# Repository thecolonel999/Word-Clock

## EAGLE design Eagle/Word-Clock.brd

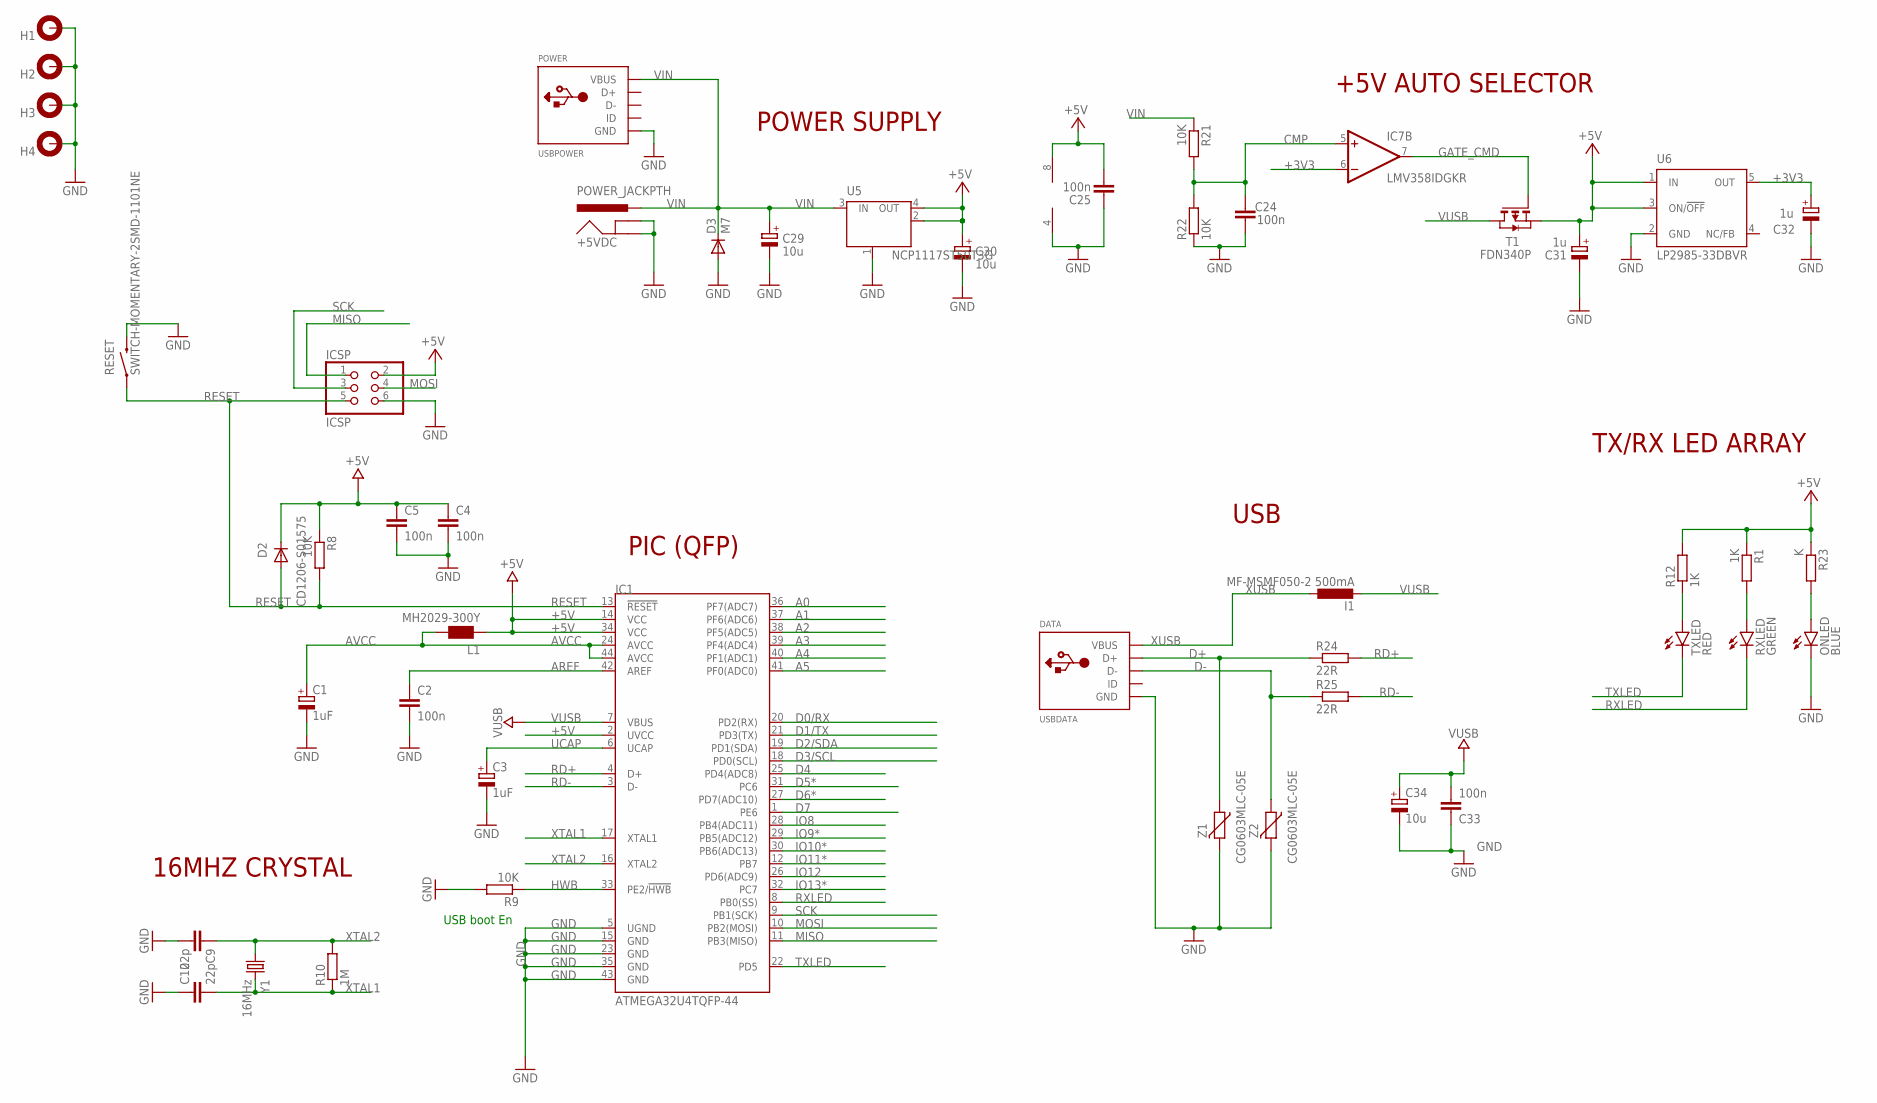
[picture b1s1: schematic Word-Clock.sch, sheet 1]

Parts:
+5VDC: POWER_JACKPTH; POWER_JACK_PTH
C1, C3: 1uF; B/3528-21W
C2, C4, C5, C24, C25, C33: 100n; C1206
C9, C10: 22p; C1206
C29, C30, C34: 10u; B/3528-21W
C31, C32: 1u; B/3528-21W
D2: CD1206-S01575; MINIMELF
D3: M7; SMB
DATA: USBDATA; USB-MINIB-THM-MOLEX
H1, H2, H3, H4: MOUNT-PAD-ROUND2.8; 2,8-PAD
I1: MF-MSMF050-2 500mA; L1812
IC1: ATMEGA32U4TQFP-44; TQFP44
IC7: LMV358IDGKR; SO08
ICSP: ICSP; 2X03/90
L1: MH2029-300Y; 0805
ONLED: BLUE; LED-1206; FARNELL 2322084
POWER: USBPOWER; USB-MINIB-THM-MOLEX
R1, R12: 1K; R1206
R8, R9, R21, R22: 10K; R1206
R10: 1M; R1206
R23: K; R1206
R24, R25: 22R; R1206
RESET: SWITCH-MOMENTARY-2SMD-1101NE; TACTILE-SWITCH-1101NE
RXLED: GREEN; LED-1206; FARNELL 2322085
T1: FDN340P; SOT-23
TXLED: RED; LED-1206
U5: NCP1117ST50T3G; SOT223; FARNELL 1147874
U6: LP2985-33DBVR; SOT23-DBV
Y1: 16MHz; HC49UP
Z1, Z2: CG0603MLC-05E; CT/CN0603

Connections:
+3V3: C32.+, IC7.6 (-IN), U6.5 (OUT)
+5V: C4.1, C5.1, C25.2, C30.+, C31.+, D2.C, IC1.2 (UVCC), IC1.14 (VCC), IC1.34 (VCC), IC7.8 (V+), ICSP.2, L1.1, R1.1, R8.1, R12.2, R23.1, T1.2 (S), U5.2 (OUT), U5.4 (OUT), U6.1 (IN), U6.3 (ON/!OFF); also elsewhere on the board
A0: IC1.36 (PF7(ADC7)); also elsewhere on the board
A1: IC1.37 (PF6(ADC6)); also elsewhere on the board
A2: IC1.38 (PF5(ADC5)); also elsewhere on the board
A3: IC1.39 (PF4(ADC4)); also elsewhere on the board
A4: IC1.40 (PF1(ADC1)); also elsewhere on the board
A5: IC1.41 (PF0(ADC0)); also elsewhere on the board
AREF: C2.1, IC1.42 (AREF)
AVCC: C1.+, IC1.24 (AVCC), IC1.44 (AVCC), L1.2
CMP: C24.2, IC7.5 (+IN), R21.2, R22.2
D0/RX: IC1.20 (PD2(RX)); also elsewhere on the board
D1/TX: IC1.21 (PD3(TX)); also elsewhere on the board
D2/SDA: IC1.19 (PD1(SDA)); also elsewhere on the board
D3/SCL: IC1.18 (PD0(SCL)); also elsewhere on the board
D4: IC1.25 (PD4(ADC8)); also elsewhere on the board
D5*: IC1.31 (PC6); also elsewhere on the board
D6*: IC1.27 (PD7(ADC10)); also elsewhere on the board
D7: IC1.1 (PE6); also elsewhere on the board
D+: DATA.D+, R24.1, Z1.1
D-: DATA.D-, R25.1, Z2.1
GATE_CMD: IC7.7 (OUT), T1.3 (G)
GND: +5VDC.GND, +5VDC.GNDBREAK, C1.-, C2.2, C3.-, C4.2, C5.2, C9.2, C10.1, C24.1, C25.1, C29.-, C30.-, C31.-, C32.-, C33.1, C34.-, D3.A, DATA.GND, H1.B2,8, H2.B2,8, H3.B2,8, H4.B2,8, IC1.5 (UGND), IC1.15 (GND), IC1.23 (GND), IC1.35 (GND), IC1.43 (GND), IC7.4 (V-), ICSP.6, ONLED.C, POWER.GND, R9.2, R22.1, RESET.2, U5.1 (GND/ADJ), U6.2 (GND), Z1.2, Z2.2; also elsewhere on the board
HWB: IC1.33 (PE2/!HWB), R9.1
IO8: IC1.28 (PB4(ADC11)); also elsewhere on the board
IO9*: IC1.29 (PB5(ADC12)); also elsewhere on the board
IO10*: IC1.30 (PB6(ADC13)); also elsewhere on the board
IO11*: IC1.12 (PB7); also elsewhere on the board
IO12: IC1.26 (PD6(ADC9)); also elsewhere on the board
IO13*: IC1.32 (PC7); also elsewhere on the board
MISO: IC1.11 (PB3(MISO)), ICSP.1
MOSI: IC1.10 (PB2(MOSI)), ICSP.4
unnamed: R12.1, TXLED.A
unnamed: R1.2, RXLED.A
unnamed: ONLED.A, R23.2
RD+: IC1.4 (D+), R24.2
RD-: IC1.3 (D-), R25.2
RESET: D2.A, IC1.13 (!RESET), ICSP.5, R8.2, RESET.1
RXLED: IC1.8 (PB0(SS)), RXLED.C
SCK: IC1.9 (PB1(SCK)), ICSP.3
TXLED: IC1.22 (PD5), TXLED.C
UCAP: C3.+, IC1.6 (UCAP)
VIN: +5VDC.PWR, C29.+, D3.C, POWER.VBUS, R21.1, U5.3 (IN); also elsewhere on the board
VUSB: C33.2, C34.+, I1.2, IC1.7 (VBUS), T1.1 (D)
XTAL1: C10.2, IC1.17 (XTAL1), R10.1, Y1.2
XTAL2: C9.1, IC1.16 (XTAL2), R10.2, Y1.1
XUSB: DATA.VBUS, I1.1

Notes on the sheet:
USB boot En
USB
+5V AUTO SELECTOR
PIC (QFP)
TX/RX LED ARRAY
16MHZ CRYSTAL
POWER SUPPLY

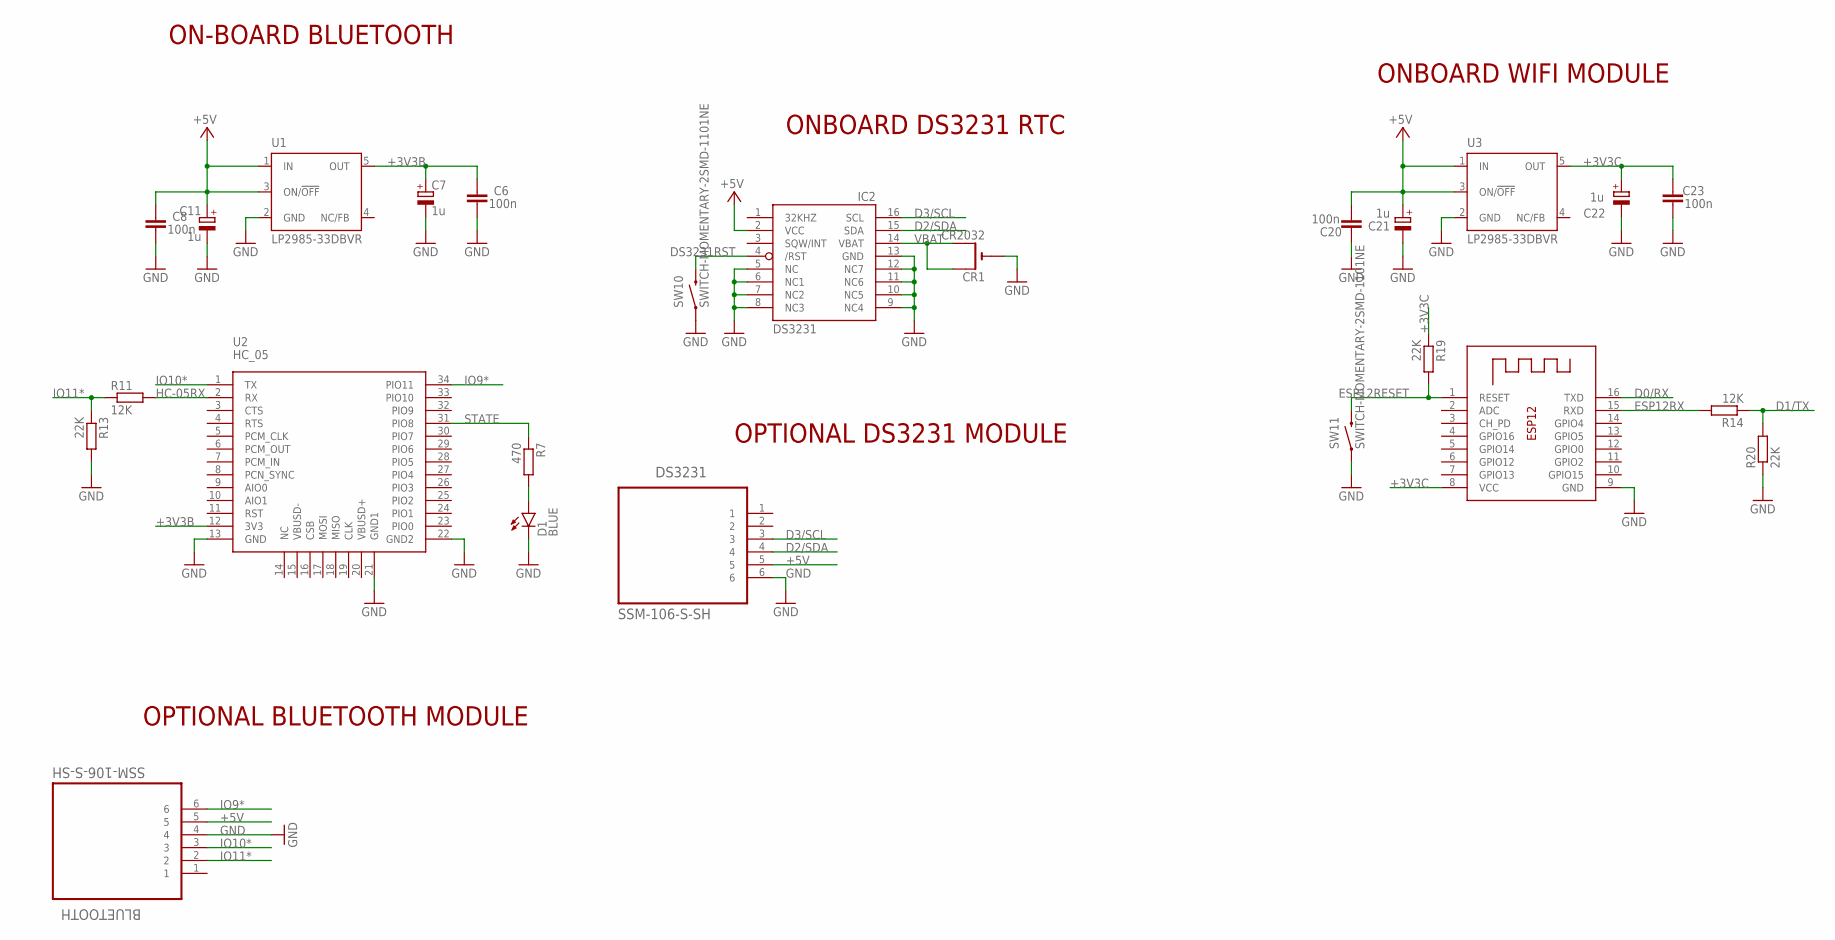
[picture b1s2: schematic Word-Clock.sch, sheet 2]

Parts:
BLUETOOTH: SSM-106-S-SH; SAMTEC_SSM-106-S-SH
C6, C8, C20, C23: 100n; C1206
C7, C11, C21, C22: 1u; B/3528-21W
CR1: CR2032; CR2032-SMD
D1: BLUE; LED-1206
DS3231: SSM-106-S-SH; SAMTEC_SSM-106-S-SH
ESP12: ESP12; ESP-12
IC2: DS3231/SO; SO16W
R7: 470; R1206
R11, R14: 12K; R1206
R13, R19, R20: 22K; R1206
SW10, SW11: SWITCH-MOMENTARY-2SMD-1101NE; TACTILE-SWITCH-1101NE
U1, U3: LP2985-33DBVR; SOT23-DBV
U2: HC_05; BLUETOOTH_SMD

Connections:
+3V3B: C6.2, C7.+, U1.5 (OUT), U2.12 (3V3)
+3V3C: C22.+, C23.2, ESP12.8 (VCC), R19.1, U3.5 (OUT)
+5V: BLUETOOTH.5, C8.2, C11.+, C20.1, C21.+, DS3231.5, IC2.2 (VCC), U1.1 (IN), U1.3 (ON/!OFF), U3.1 (IN), U3.3 (ON/!OFF); also elsewhere on the board
BLUETOOTHLED: D1.A, R7.2
D0/RX: ESP12.16 (TXD); also elsewhere on the board
D1/TX: R14.1, R20.2; also elsewhere on the board
D2/SDA: DS3231.4, IC2.15 (SDA); also elsewhere on the board
D3/SCL: DS3231.3, IC2.16 (SCL); also elsewhere on the board
DS3231RST: IC2.4 (/RST), SW10.2
ESP12RESET: ESP12.1 (RESET), R19.2, SW11.2
ESP12RX: ESP12.15 (RXD), R14.2
GND: BLUETOOTH.4, C6.1, C7.-, C8.1, C11.-, C20.2, C21.-, C22.-, C23.1, CR1.-, D1.C, DS3231.6, ESP12.9 (GND), IC2.5 (NC), IC2.6 (NC1), IC2.7 (NC2), IC2.8 (NC3), IC2.9 (NC4), IC2.10 (NC5), IC2.11 (NC6), IC2.12 (NC7), IC2.13 (GND), R13.2, R20.1, SW10.1, SW11.1, U1.2 (GND), U2.13 (GND), U2.21 (GND1), U2.22 (GND2), U3.2 (GND); also elsewhere on the board
HC-05RX: R11.2, U2.2 (RX)
IO9*: BLUETOOTH.6, U2.34 (PIO11); also elsewhere on the board
IO10*: BLUETOOTH.3, U2.1 (TX); also elsewhere on the board
IO11*: BLUETOOTH.2, R11.1, R13.1; also elsewhere on the board
STATE: R7.1, U2.31 (PIO8)
VBAT: CR1.+$1 (+), CR1.+$2 (+1), IC2.14 (VBAT)

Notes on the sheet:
ONBOARD DS3231 RTC
OPTIONAL BLUETOOTH MODULE
ON-BOARD BLUETOOTH
OPTIONAL DS3231 MODULE
ONBOARD WIFI MODULE

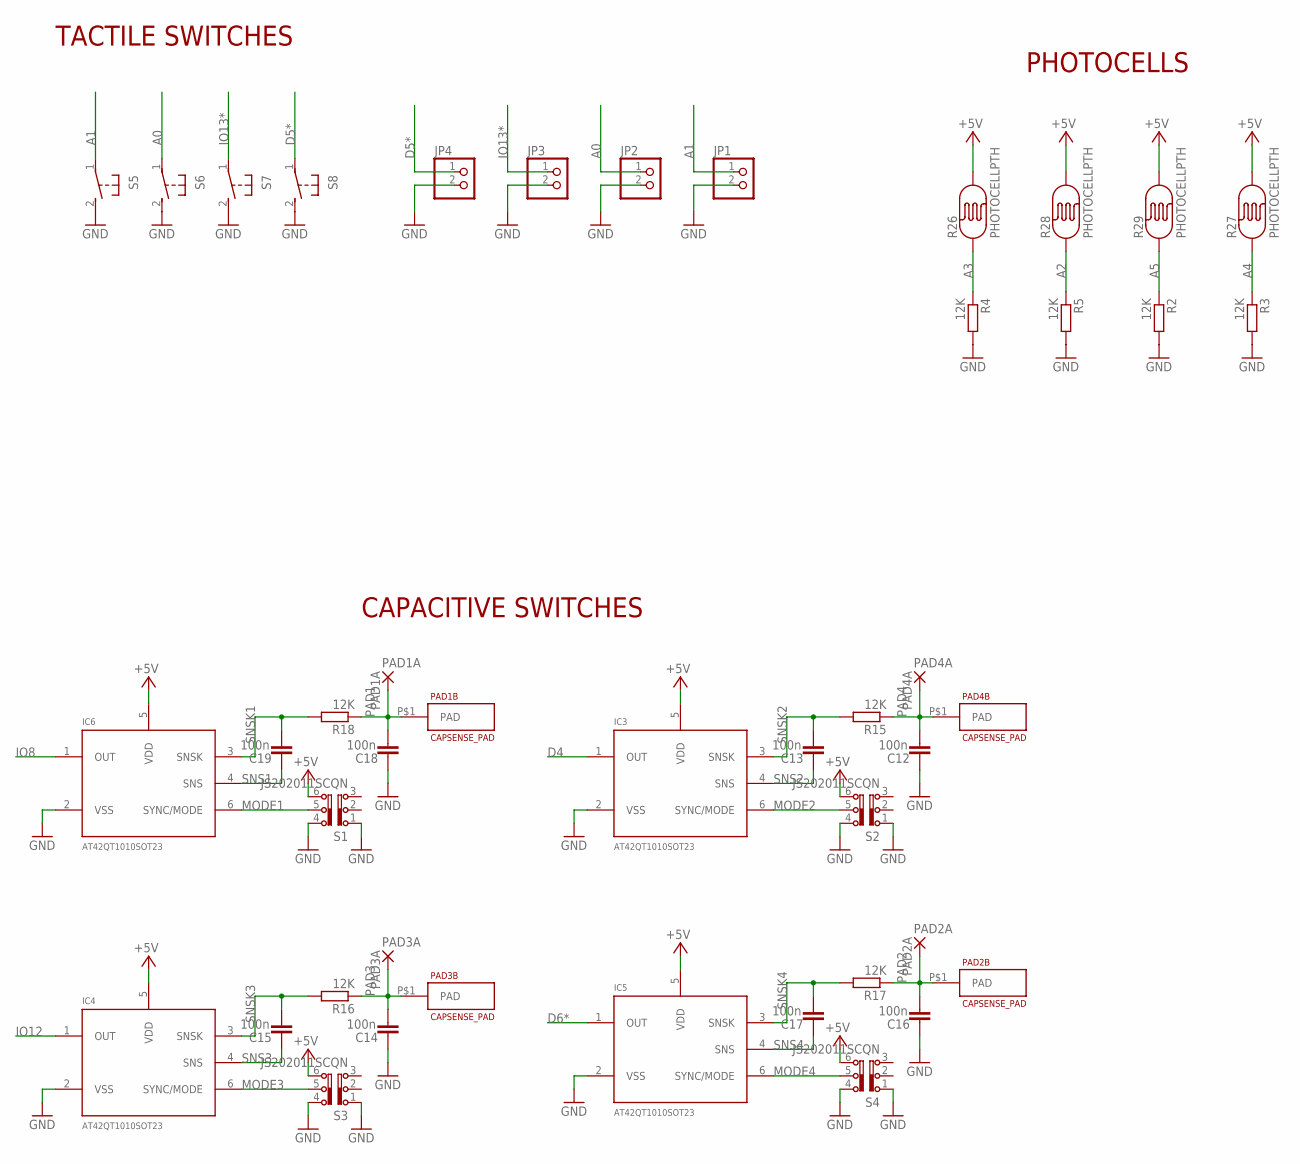
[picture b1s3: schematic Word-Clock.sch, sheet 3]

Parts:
C12, C13, C14, C15, C16, C17, C18, C19: 100n; C1206
IC3, IC4, IC5, IC6: AT42QT1010SOT23; SOT23-6
JP1, JP2, JP3, JP4: PINHD-1X2/90; 1X02/90
PAD1A: PAD1A; 2,54/1,0
PAD1B, PAD2B, PAD3B, PAD4B: CAPSENSE_PAD
PAD2A: PAD2A; 2,54/1,0
PAD3A: PAD3A; 2,54/1,0
PAD4A: PAD4A; 2,54/1,0
R2, R3, R4, R5, R15, R16, R17, R18: 12K; R1206
R26, R27, R28, R29: PHOTOCELLPTH; PHOTOCELL
S1, S2, S3, S4: JS202011SCQN
S5, S6, S7, S8: 31-XX; B3F-31XX

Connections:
+5V: IC3.5 (VDD), IC4.5 (VDD), IC5.5 (VDD), IC6.5 (VDD), R26.2, R27.2, R28.2, R29.2, S1.6, S2.6, S3.6, S4.6; also elsewhere on the board
A0: JP2.1, S6.1; also elsewhere on the board
A1: JP1.1, S5.1; also elsewhere on the board
A2: R5.1, R28.1; also elsewhere on the board
A3: R4.1, R26.1; also elsewhere on the board
A4: R3.1, R27.1; also elsewhere on the board
A5: R2.1, R29.1; also elsewhere on the board
D4: IC3.1 (OUT); also elsewhere on the board
D5*: JP4.1, S8.1; also elsewhere on the board
D6*: IC5.1 (OUT); also elsewhere on the board
GND: C12.2, C14.2, C16.2, C18.2, IC3.2 (VSS), IC4.2 (VSS), IC5.2 (VSS), IC6.2 (VSS), JP1.2, JP2.2, JP3.2, JP4.2, R2.2, R3.2, R4.2, R5.2, S1.1, S1.4, S2.1, S2.4, S3.1, S3.4, S4.1, S4.4, S5.2 (S), S6.2 (S), S7.2 (S), S8.2 (S); also elsewhere on the board
IO8: IC6.1 (OUT); also elsewhere on the board
IO12: IC4.1 (OUT); also elsewhere on the board
IO13*: JP3.1, S7.1; also elsewhere on the board
MODE1: IC6.6 (SYNC/MODE), S1.5
MODE2: IC3.6 (SYNC/MODE), S2.5
MODE3: IC4.6 (SYNC/MODE), S3.5
MODE4: IC5.6 (SYNC/MODE), S4.5
PAD1: C18.1, PAD1A.1, PAD1B.P$1, R18.1
PAD2: C16.1, PAD2A.1, PAD2B.P$1, R17.1
PAD3: C14.1, PAD3A.1, PAD3B.P$1, R16.1
PAD4: C12.1, PAD4A.1, PAD4B.P$1, R15.1
SNS1: C19.2, IC6.4 (SNS)
SNS2: C13.2, IC3.4 (SNS)
SNS3: C15.2, IC4.4 (SNS)
SNS4: C17.2, IC5.4 (SNS)
SNSK1: C19.1, IC6.3 (SNSK), R18.2
SNSK2: C13.1, IC3.3 (SNSK), R15.2
SNSK3: C15.1, IC4.3 (SNSK), R16.2
SNSK4: C17.1, IC5.3 (SNSK), R17.2

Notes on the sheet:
CAPACITIVE SWITCHES
TACTILE SWITCHES
PHOTOCELLS

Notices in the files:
parts and their libraries:
SparkFun-LED: Licensing: Creative Commons ShareAlike 4.0 International - https://creativecommons.org/licenses/by-sa/4.0
switch-ck: Copyright (C) 2011, Bob Starr
